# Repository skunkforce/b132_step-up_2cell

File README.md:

# edgy_board number b132
This design is part of the [edgy board project](https://github.com/skunkforce/edgy_boards). It provides the functionality of chip XXXX via interfaces YYYY. 

# getting started
This repository uses submodules. After cloning use the command 

```$ git submodule update --init --recursive```

to pull the submodules before opening the project with kicad. 

# Tests
Tests can be found in [TESTS.md](TESTS.md)

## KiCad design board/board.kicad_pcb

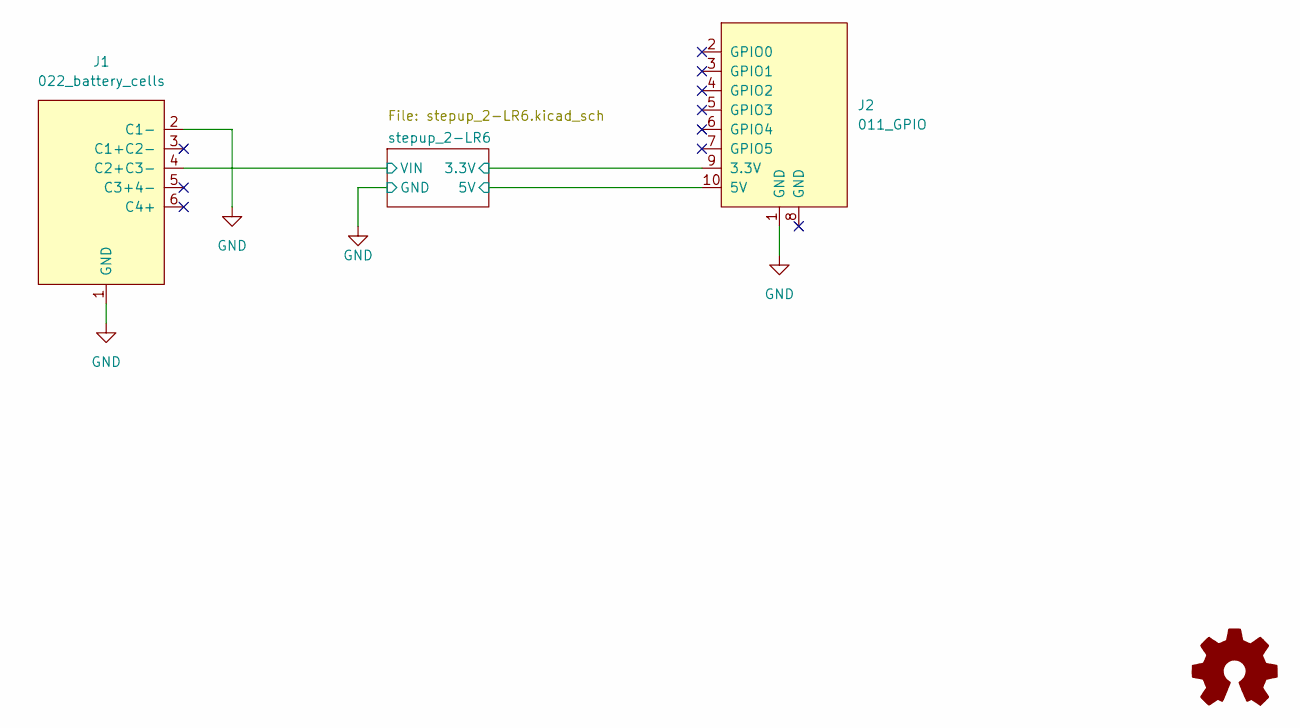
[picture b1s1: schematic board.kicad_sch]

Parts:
J1: 022_battery_cells; on_edge_2x05_device
J2: 011_GPIO; on_edge_2x05_host
LOGO1: Logo_Open_Hardware_Small; OSHW-Symbol_6.7x6mm_SilkScreen

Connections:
/stepup_2-LR6/3.3V: J2.9 (3.3V); also elsewhere on the board
/stepup_2-LR6/5V: J2.10 (5V); also elsewhere on the board
/stepup_2-LR6/VIN: J1.4 (C2+C3-); also elsewhere on the board
GND: J1.1 (GND), J1.2 (C1-), J2.1 (GND); also elsewhere on the board

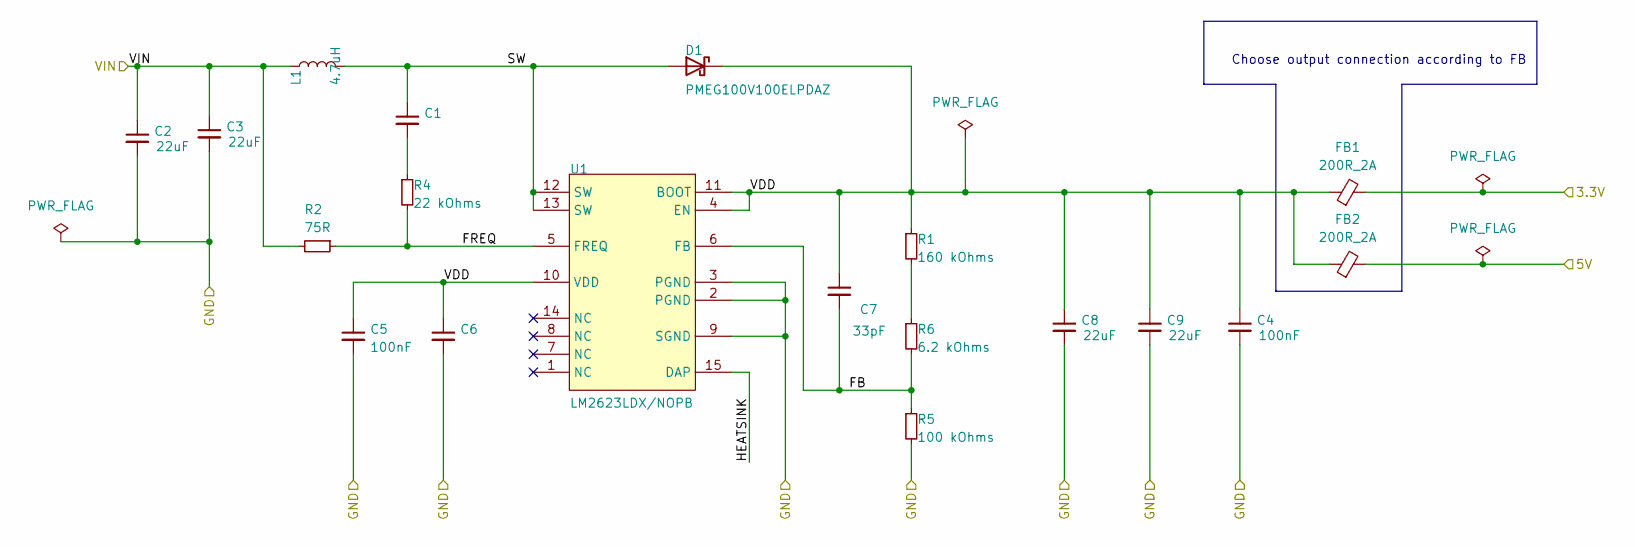
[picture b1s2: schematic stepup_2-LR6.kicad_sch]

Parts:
C1: 4.7pF; C_0402_1005Metric
C2, C3, C8, C9: 22uF; C_0805_2012Metric
C4, C6: 100nF; C_0402_1005Metric
C5: 100nF; C_0402_1005Metric; RATINGS AEC-Q200; TOLERANCE ±10%; PART NUMBER AC0402KRX7R7BB104
C7: 33pF; C_0603_1608Metric; VOLTAGE RATING (DC) 50V; TOLERANCE 5%
D1: PMEG100V100ELPDAZ
FB1, FB2: 200R_2A; L_0805_2012Metric
L1: 4.7uH; WURTH 5040; CURRENT RATING (AMPS) 4.6 A; RATINGS AEC-Q200; PART NUMBER 744316470
R1: 160 kOhms; R_0603_1608Metric; RATINGS AEC-Q200; TOLERANCE ±1%; PART NUMBER RK73H1ETTP1603F
R2: 75R; R_0603_1608Metric
R4: 22 kOhms; R_0603_1608Metric; RATINGS AEC-Q200; TOLERANCE ±1%; PART NUMBER CRGCQ0402F22K
R5: 100 kOhms; R_0603_1608Metric; TOLERANCE ±1%; PART NUMBER RC0402FR-07100KL
R6: 6.2 kOhms; R_0603_1608Metric; RATINGS AEC-Q200; TOLERANCE ±1%; PART NUMBER RK73H1ETTP6201F
U1: LM2623LDX/NOPB; NHE0014A_V

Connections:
/stepup_2-LR6/3.3V: FB1.2; also elsewhere on the board
/stepup_2-LR6/5V: FB2.2; also elsewhere on the board
/stepup_2-LR6/FB: C7.2, R5.1, R6.2, U1.6 (FB)
/stepup_2-LR6/FREQ: R2.1, R4.2, U1.5 (FREQ)
/stepup_2-LR6/HEATSINK: U1.15 (DAP)
/stepup_2-LR6/SW: C1.1, D1.1 (A), D1.2 (A), L1.2, U1.12 (SW), U1.13 (SW)
/stepup_2-LR6/VDD: C4.1, C5.1, C6.1, C7.1, C8.1, C9.1, D1.3 (K), FB1.1, FB2.1, R1.1, U1.4 (EN), U1.10 (VDD), U1.11 (BOOT)
/stepup_2-LR6/VIN: C2.1, C3.1, L1.1, R2.2; also elsewhere on the board
GND: C2.2, C3.2, C4.2, C5.2, C6.2, C8.2, C9.2, R5.2, U1.2 (PGND), U1.3 (PGND), U1.9 (SGND); also elsewhere on the board
unnamed: R1.2, R6.1
unnamed: C1.2, R4.1

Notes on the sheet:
Choose output connection according to FB

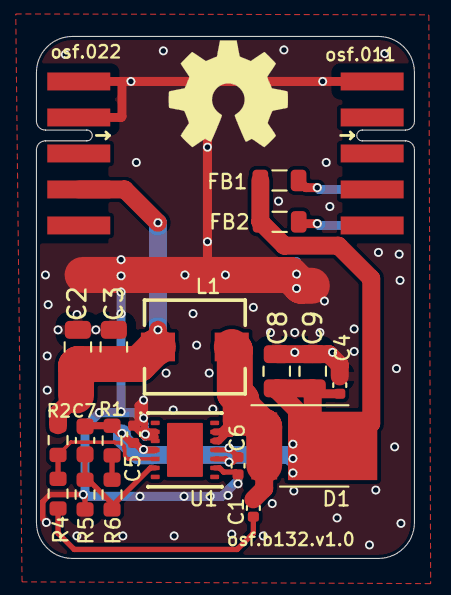
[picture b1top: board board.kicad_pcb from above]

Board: 2 copper layers, 21.0 x 29.0 mm, 22 parts (0 on the bottom side), 10 nets.

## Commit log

2023-05-09 Initial design
2023-05-09 Update implementation name
2023-05-09 Update README.md
    fix numbering
2023-05-15 switched edge connectors to use the correct footprints and renamed local libraries to fit with the edgy naming convention
2023-05-15 changed constraints to work as a 2 layer board, changed symbols to kicad native
2023-06-05 switched to ceramic caps
